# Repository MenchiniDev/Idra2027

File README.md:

# Idra di Guerra

Elettronica e meccanica per il carro **"Idra di Guerra"** — Carnevale di Viareggio.

## Obiettivi
- **PCB (KiCad)**: scheda EyeNode per ogni testa (servo degli occhi), alimentazione da 2 × 6 V piombo in serie (12 V).
- **Firmware**: ogni testa muove gli occhi in modo autonomo e casuale, senza sincronia tra le teste.
- **Requisiti elettrici**: budget energetico, dimensionamento alimentatori, sezione cavi, protezioni.
- **Meccanica 3D**: occhi (Ø ≥ 50 mm), incavo/orbita, meccanismo di movimento, supporto servo.
- **Chassis**: contenitori per l'elettronica, cablaggio ordinato e manutenibile.

## Struttura
```
docs/                  requisiti, budget energetico, cablaggio
hardware/kicad/        progetto KiCad (schematico + PCB)
hardware/datasheets/   datasheet componenti
mechanical/eyes/       original/ = 2 modelli di partenza, eyemech_D85/ = occhi in uso, idra_version/ = versione in scala di Will
mechanical/legs/       pezzi delle gambe
mechanical/enclosures/ chassis per l'elettronica
mechanical/scripts/    script di generazione/scalatura dei modelli
firmware/              codice delle schede EyeNode (movimento casuale autonomo)
```

## Regola chiave per gli occhi
Il bulbo va ingrandito a **diametro ≥ 50 mm**, ma la **sede del servo resta in scala 1:1**
(i servomotori sono fissi e non cambiano dimensione).

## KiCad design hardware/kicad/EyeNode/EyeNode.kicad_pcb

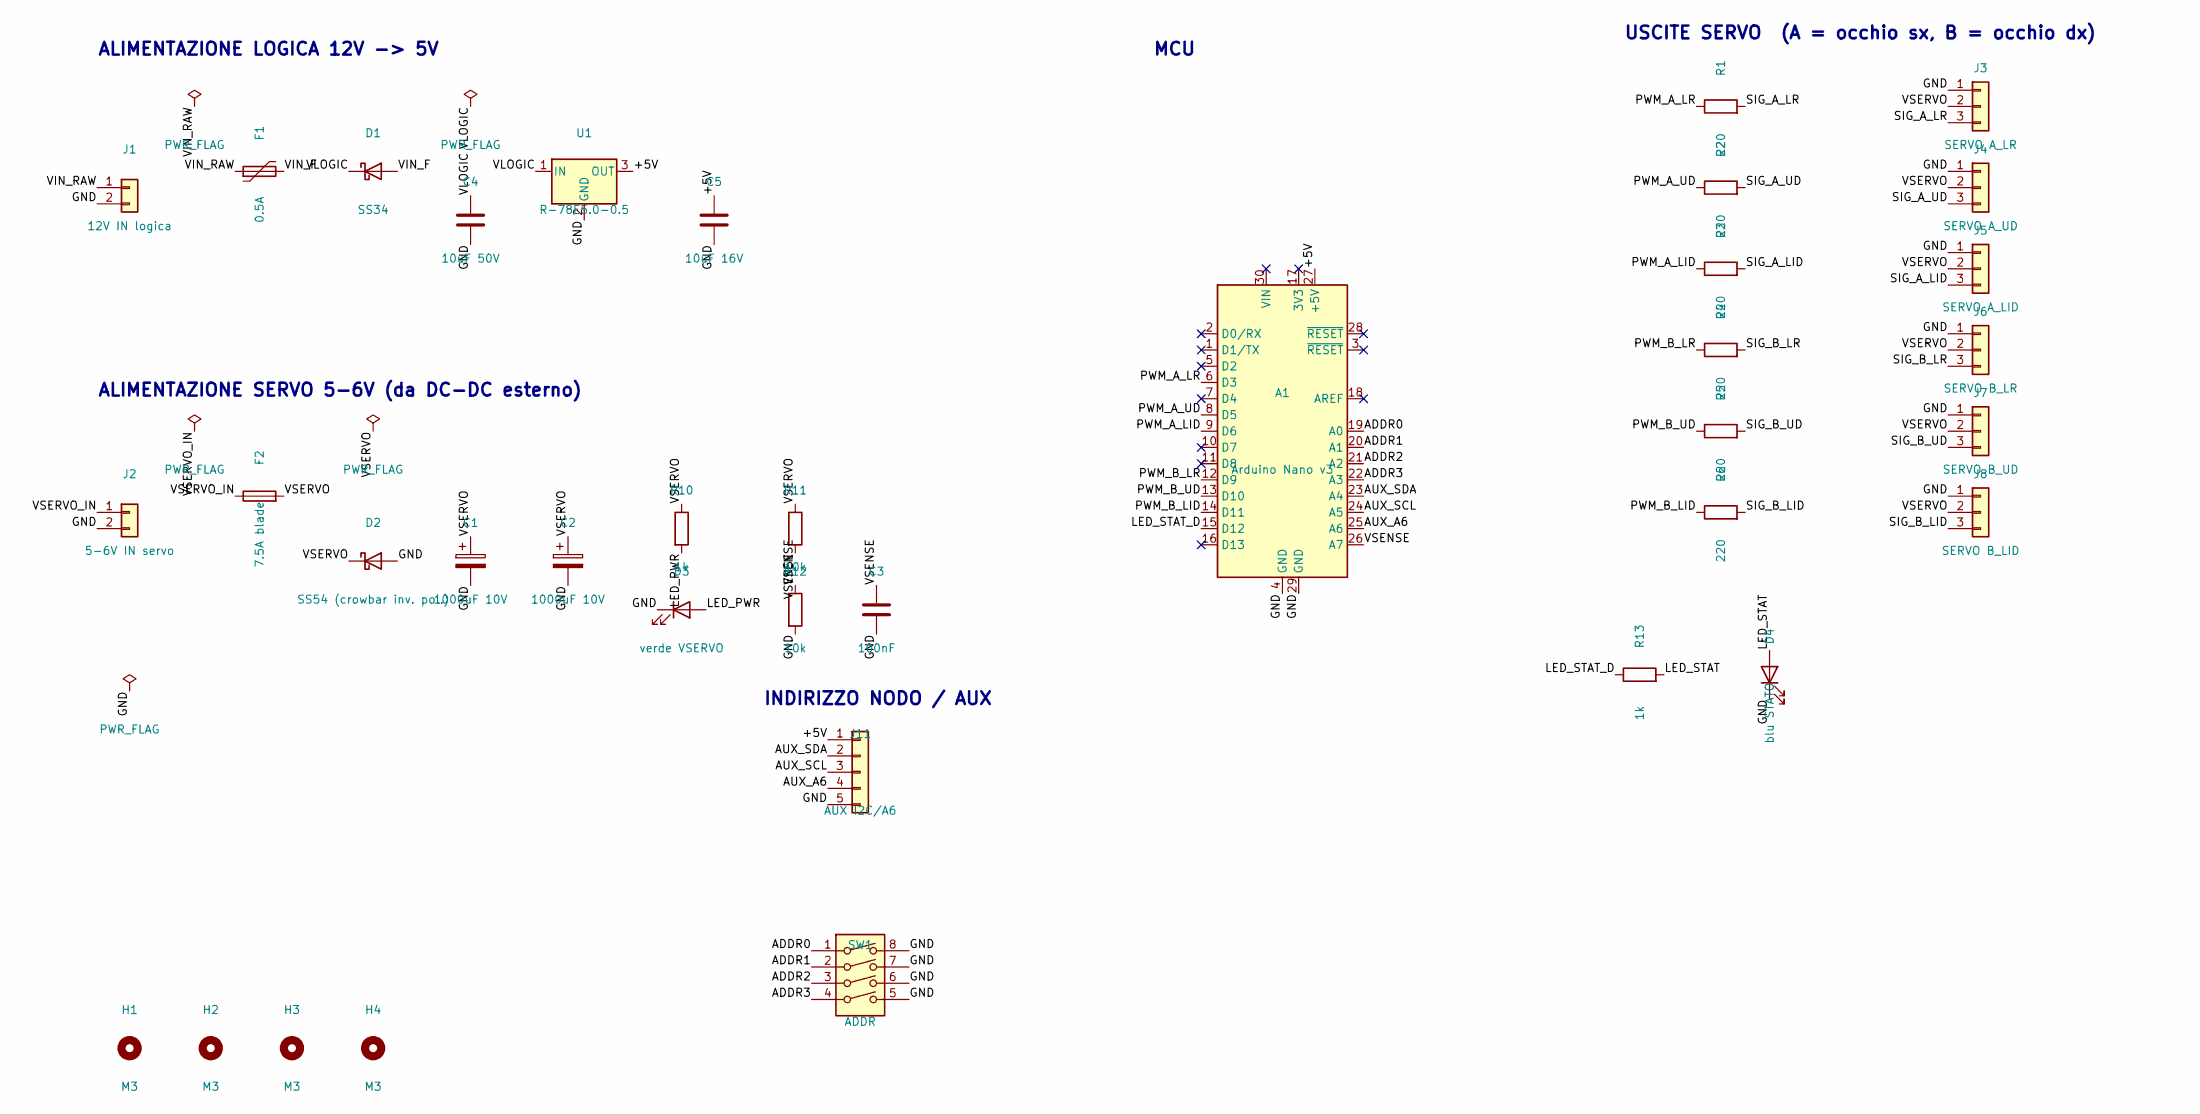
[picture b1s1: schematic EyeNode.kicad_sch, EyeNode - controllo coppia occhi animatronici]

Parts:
A1: Arduino Nano v3; Arduino_Nano
C1, C2: 1000uF 10V; CP_Radial_D10.0mm_P5.00mm
C3: 100nF; C_1206_3216Metric
C4: 10uF 50V; C_1206_3216Metric
C5: 10uF 16V; C_1206_3216Metric
D1: SS34; D_SMA
D2: SS54 (crowbar inv. pol.); D_SMC
D3: verde VSERVO; LED_1206_3216Metric
D4: blu STATO; LED_1206_3216Metric
F1: 0.5A; Fuse_1812_4532Metric
F2: 7.5A blade; Fuseholder_Blade_Mini_Keystone_3568
H1, H2, H3, H4: M3; MountingHole_3.2mm_M3
J1: 12V IN logica; TerminalBlock_Phoenix_MKDS-1,5-2-5.08_1x02_P5.08mm_Horizont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
J2: 5-6V IN servo; TerminalBlock_Phoenix_MKDS-1,5-2-5.08_1x02_P5.08mm_Horizont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
J3: SERVO A_LR; PinHeader_1x03_P2.54mm_Vertical
J4: SERVO A_UD; PinHeader_1x03_P2.54mm_Vertical
J5: SERVO A_LID; PinHeader_1x03_P2.54mm_Vertical
J6: SERVO B_LR; PinHeader_1x03_P2.54mm_Vertical
J7: SERVO B_UD; PinHeader_1x03_P2.54mm_Vertical
J8: SERVO B_LID; PinHeader_1x03_P2.54mm_Vertical
J11: AUX I2C/A6; PinHeader_1x05_P2.54mm_Vertical
R1, R2, R3, R4, R5, R6: 220; R_1206_3216Metric
R10, R13: 1k; R_1206_3216Metric
R11, R12: 10k; R_1206_3216Metric
SW1: ADDR; SW_DIP_SPSTx04_Slide_9.78x12.34mm_W7.62mm_P2.54mm
U1: R-78E5.0-0.5; Converter_DCDC_RECOM_R-78E-0.5_THT

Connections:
/+5V: A1.27 (+5V), C5.1, J11.1, U1.3 (OUT)
/ADDR0: A1.19 (A0), SW1.1
/ADDR1: A1.20 (A1), SW1.2
/ADDR2: A1.21 (A2), SW1.3
/ADDR3: A1.22 (A3), SW1.4
/AUX_A6: A1.25 (A6), J11.4
/AUX_SCL: A1.24 (A5), J11.3
/AUX_SDA: A1.23 (A4), J11.2
/GND: A1.4 (GND), A1.29 (GND), C1.2, C2.2, C3.2, C4.2, C5.2, D2.2 (A), D3.1 (K), D4.1 (K), J1.2, J2.2, J3.1, J4.1, J5.1, J6.1, J7.1, J8.1, J11.5, R12.2, SW1.5, SW1.6, SW1.7, SW1.8, U1.2 (GND)
/LED_PWR: D3.2 (A), R10.2
/LED_STAT: D4.2 (A), R13.2
/LED_STAT_D: A1.15 (D12), R13.1
/PWM_A_LID: A1.9 (D6), R3.1
/PWM_A_LR: A1.6 (D3), R1.1
/PWM_A_UD: A1.8 (D5), R2.1
/PWM_B_LID: A1.14 (D11), R6.1
/PWM_B_LR: A1.12 (D9), R4.1
/PWM_B_UD: A1.13 (D10), R5.1
/SIG_A_LID: J5.3, R3.2
/SIG_A_LR: J3.3, R1.2
/SIG_A_UD: J4.3, R2.2
/SIG_B_LID: J8.3, R6.2
/SIG_B_LR: J6.3, R4.2
/SIG_B_UD: J7.3, R5.2
/VIN_F: D1.2 (A), F1.2
/VIN_RAW: F1.1, J1.1
/VLOGIC: C4.1, D1.1 (K), U1.1 (IN)
/VSENSE: A1.26 (A7), C3.1, R11.2, R12.1
/VSERVO: C1.1, C2.1, D2.1 (K), F2.2, J3.2, J4.2, J5.2, J6.2, J7.2, J8.2, R10.1, R11.1
/VSERVO_IN: F2.1, J2.1

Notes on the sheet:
ALIMENTAZIONE LOGICA 12V -> 5V
ALIMENTAZIONE SERVO 5-6V (da DC-DC esterno)
MCU
USCITE SERVO (A = occhio sx, B = occhio dx)
INDIRIZZO NODO / AUX

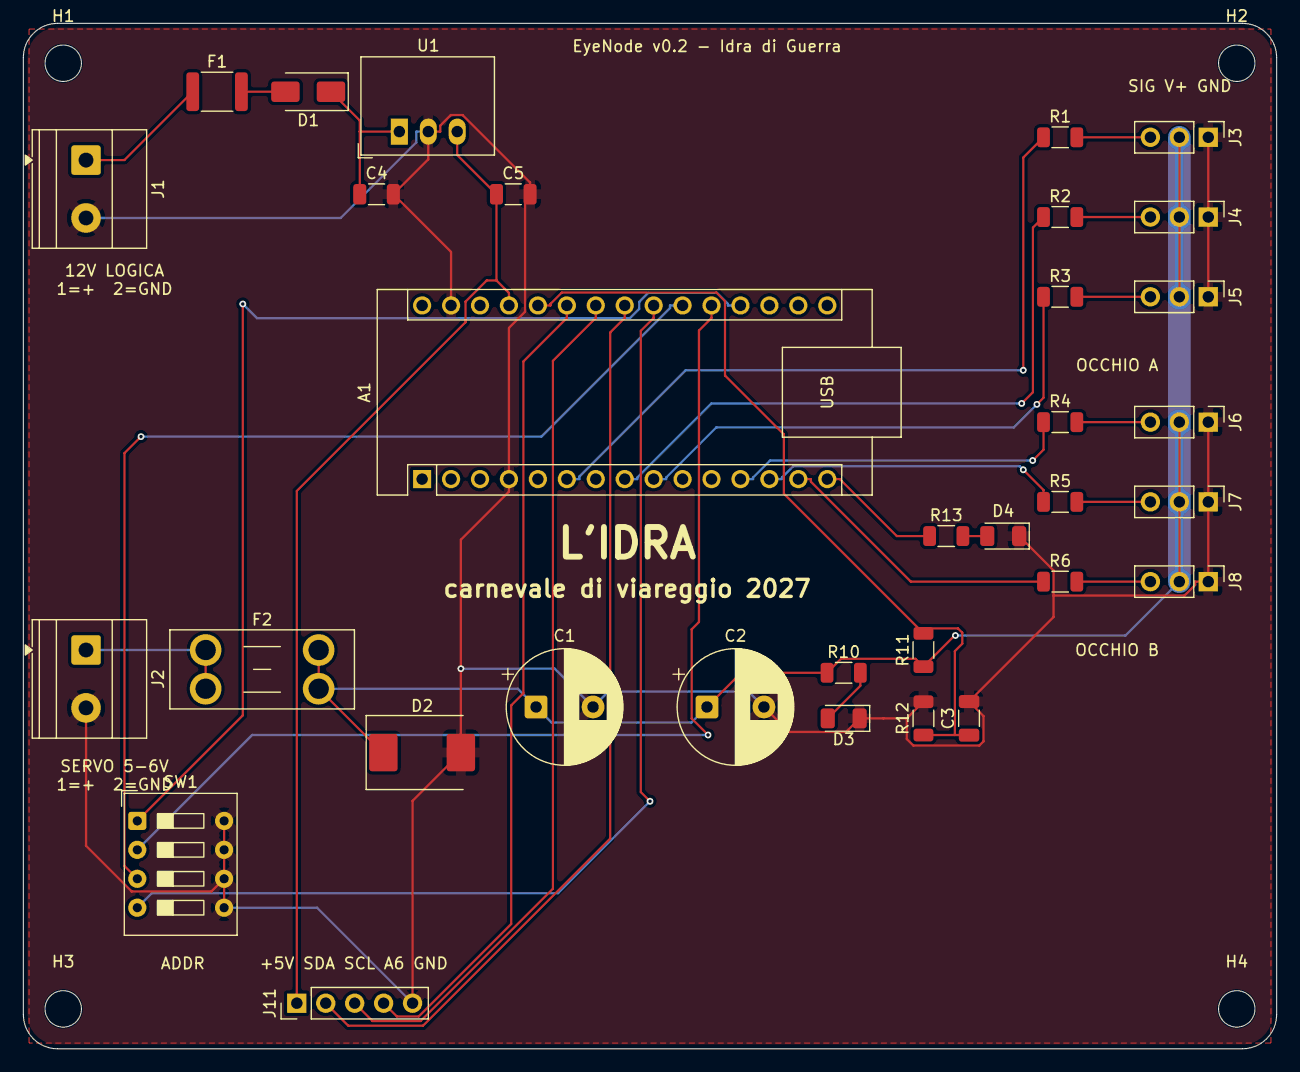
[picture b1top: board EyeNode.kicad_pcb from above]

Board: 2 copper layers, 110.0 x 90.0 mm, 37 parts (0 on the bottom side), 30 nets.

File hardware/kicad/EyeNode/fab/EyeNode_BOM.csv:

"Riferimenti","Valore","Footprint","Qta"
"A1","Arduino Nano v3","Module:Arduino_Nano","1"
"C1,C2","1000uF 10V","Capacitor_THT:CP_Radial_D10.0mm_P5.00mm","2"
"C3","100nF","Capacitor_SMD:C_1206_3216Metric","1"
"C4","10uF 50V","Capacitor_SMD:C_1206_3216Metric","1"
"C5","10uF 16V","Capacitor_SMD:C_1206_3216Metric","1"
"D1","SS34","Diode_SMD:D_SMA","1"
"D2","SS54 (crowbar inv. pol.)","Diode_SMD:D_SMC","1"
"D3","verde VSERVO","LED_SMD:LED_1206_3216Metric","1"
"D4","blu STATO","LED_SMD:LED_1206_3216Metric","1"
"F1","0.5A","Fuse:Fuse_1812_4532Metric","1"
"F2","7.5A blade","Fuse:Fuseholder_Blade_Mini_Keystone_3568","1"
"J1","12V IN logica","TerminalBlock_Phoenix:TerminalBlock_Phoenix_MKDS-1,5-2-5.08_1x02_P5.08mm_Horizontal","1"
"J2","5-6V IN servo","TerminalBlock_Phoenix:TerminalBlock_Phoenix_MKDS-1,5-2-5.08_1x02_P5.08mm_Horizontal","1"
"J3","SERVO A_LR","Connector_PinHeader_2.54mm:PinHeader_1x03_P2.54mm_Vertical","1"
"J4","SERVO A_UD","Connector_PinHeader_2.54mm:PinHeader_1x03_P2.54mm_Vertical","1"
"J5","SERVO A_LID","Connector_PinHeader_2.54mm:PinHeader_1x03_P2.54mm_Vertical","1"
"J6","SERVO B_LR","Connector_PinHeader_2.54mm:PinHeader_1x03_P2.54mm_Vertical","1"
"J7","SERVO B_UD","Connector_PinHeader_2.54mm:PinHeader_1x03_P2.54mm_Vertical","1"
"J8","SERVO B_LID","Connector_PinHeader_2.54mm:PinHeader_1x03_P2.54mm_Vertical","1"
"J11","AUX I2C/A6","Connector_PinHeader_2.54mm:PinHeader_1x05_P2.54mm_Vertical","1"
"R1-R6","220","Resistor_SMD:R_1206_3216Metric","6"
"R10,R13","1k","Resistor_SMD:R_1206_3216Metric","2"
"R11,R12","10k","Resistor_SMD:R_1206_3216Metric","2"
"SW1","ADDR","Button_Switch_THT:SW_DIP_SPSTx04_Slide_9.78x12.34mm_W7.62mm_P2.54mm","1"
"U1","R-78E5.0-0.5","Converter_DCDC:Converter_DCDC_RECOM_R-78E-0.5_THT","1"
